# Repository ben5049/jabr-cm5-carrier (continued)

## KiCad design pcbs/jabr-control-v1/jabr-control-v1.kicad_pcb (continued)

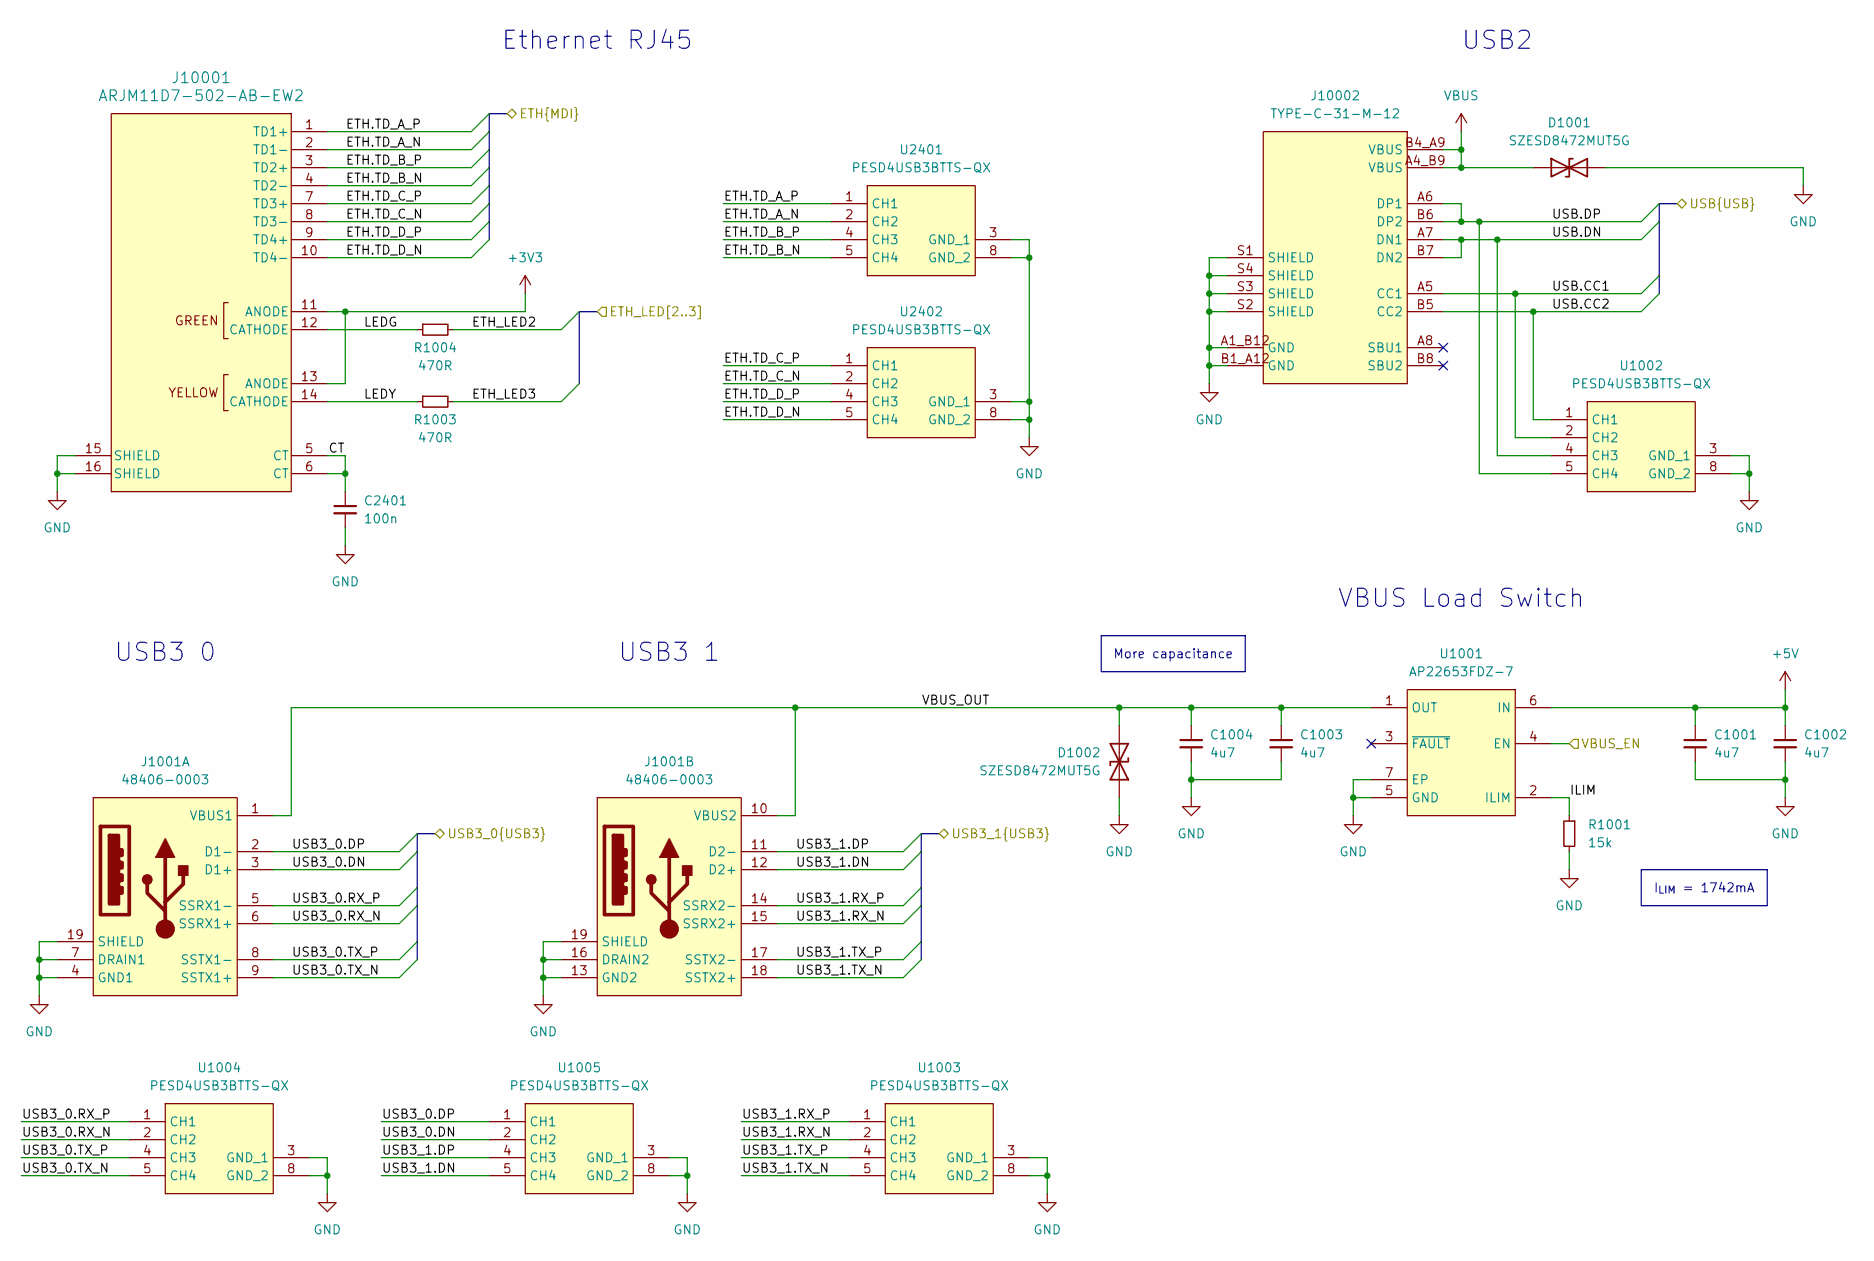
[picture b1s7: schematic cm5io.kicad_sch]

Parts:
C1001, C1002, C1003, C1004: 4u7; C_0402
C2401: 100n; C_0402
D1001, D1002: SZESD8472MUT5G; SZESD7462N2T5G
J1001: 48406-0003
J10001: ARJM11D7-502-AB-EW2; ARJM11D7-502-AB-EW2_ABR
J10002: TYPE-C-31-M-12; PARTREV 2020.12.08
R1001: 15k
R1003, R1004: 470R
U1001: AP22653FDZ-7; SON65P200X200X80-7N-D
U1002, U1003, U1004, U1005, U2401, U2402: PESD4USB3BTTS-QX; PESD4USB3BTTSQX; Mouser Part Number 771-PESD4USB3BTTS-QX

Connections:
+3V3: J10001.11 (ANODE), J10001.13 (ANODE); also elsewhere on the board
+5V: C1001.1, C1002.1, U1001.6 (IN); also elsewhere on the board
/CM5/ETH.TD_A_N: J10001.2 (TD1-), U2401.2 (CH2), U2401.9 (NC); also elsewhere on the board
/CM5/ETH.TD_A_P: J10001.1 (TD1+), U2401.1 (CH1), U2401.10 (NC); also elsewhere on the board
/CM5/ETH.TD_B_N: J10001.4 (TD2-), U2401.5 (CH4), U2401.6 (NC); also elsewhere on the board
/CM5/ETH.TD_B_P: J10001.3 (TD2+), U2401.4 (CH3), U2401.7 (NC); also elsewhere on the board
/CM5/ETH.TD_C_N: J10001.8 (TD3-), U2402.2 (CH2), U2402.9 (NC); also elsewhere on the board
/CM5/ETH.TD_C_P: J10001.7 (TD3+), U2402.1 (CH1), U2402.10 (NC); also elsewhere on the board
/CM5/ETH.TD_D_N: J10001.10 (TD4-), U2402.5 (CH4), U2402.6 (NC); also elsewhere on the board
/CM5/ETH.TD_D_P: J10001.9 (TD4+), U2402.4 (CH3), U2402.7 (NC); also elsewhere on the board
/CM5/USB2_DEV.CC1: J10002.A5 (CC1), U1002.2 (CH2), U1002.9 (NC); also elsewhere on the board
/CM5/USB2_DEV.CC2: J10002.B5 (CC2), U1002.1 (CH1), U1002.10 (NC); also elsewhere on the board
/CM5/USB2_DEV.DN: J10002.A7 (DN1), J10002.B7 (DN2), U1002.4 (CH3), U1002.7 (NC); also elsewhere on the board
/CM5/USB2_DEV.DP: J10002.A6 (DP1), J10002.B6 (DP2), U1002.5 (CH4), U1002.6 (NC); also elsewhere on the board
/CM5/USB3_0.DN: J1001.3 (D1+), U1005.2 (CH2), U1005.9 (NC); also elsewhere on the board
/CM5/USB3_0.DP: J1001.2 (D1-), U1005.1 (CH1), U1005.10 (NC); also elsewhere on the board
/CM5/USB3_0.RX_N: J1001.6 (SSRX1+), U1004.2 (CH2), U1004.9 (NC); also elsewhere on the board
/CM5/USB3_0.RX_P: J1001.5 (SSRX1-), U1004.1 (CH1), U1004.10 (NC); also elsewhere on the board
/CM5/USB3_0.TX_N: J1001.9 (SSTX1+), U1004.5 (CH4), U1004.6 (NC); also elsewhere on the board
/CM5/USB3_0.TX_P: J1001.8 (SSTX1-), U1004.4 (CH3), U1004.7 (NC); also elsewhere on the board
/CM5/USB3_1.DN: J1001.12 (D2+), U1005.5 (CH4), U1005.6 (NC); also elsewhere on the board
/CM5/USB3_1.DP: J1001.11 (D2-), U1005.4 (CH3), U1005.7 (NC); also elsewhere on the board
/CM5/USB3_1.RX_N: J1001.15 (SSRX2+), U1003.2 (CH2), U1003.9 (NC); also elsewhere on the board
/CM5/USB3_1.RX_P: J1001.14 (SSRX2-), U1003.1 (CH1), U1003.10 (NC); also elsewhere on the board
/CM5/USB3_1.TX_N: J1001.18 (SSTX2+), U1003.5 (CH4), U1003.6 (NC); also elsewhere on the board
/CM5/USB3_1.TX_P: J1001.17 (SSTX2-), U1003.4 (CH3), U1003.7 (NC); also elsewhere on the board
/CM5/VBUS_EN: U1001.4 (EN); also elsewhere on the board
/CM5IO/CT: C2401.1, J10001.5 (CT), J10001.6 (CT)
/CM5IO/ILIM: R1001.1, U1001.2 (ILIM)
/CM5IO/LEDG: J10001.12 (CATHODE), R1004.1
/CM5IO/LEDY: J10001.14 (CATHODE), R1003.1
/CM5IO/VBUS_OUT: C1003.1, C1004.1, D1002.2 (A2), J1001.1 (VBUS1), J1001.10 (VBUS2), U1001.1 (OUT)
GND: C1001.2, C1002.2, C1003.2, C1004.2, C2401.2, D1001.2 (A2), D1002.1 (A1), J1001.4 (GND1), J1001.7 (DRAIN1), J1001.13 (GND2), J1001.16 (DRAIN2), J1001.19 (SHIELD), J10001.15 (SHIELD), J10001.16 (SHIELD), J10002.A1_B12 (GND), J10002.B1_A12 (GND), J10002.S1 (SHIELD), J10002.S2 (SHIELD), J10002.S3 (SHIELD), J10002.S4 (SHIELD), R1001.2, U1001.5 (GND), U1001.7 (EP), U1002.3 (GND_1), U1002.8 (GND_2), U1003.3 (GND_1), U1003.8 (GND_2), U1004.3 (GND_1), U1004.8 (GND_2), U1005.3 (GND_1), U1005.8 (GND_2), U2401.3 (GND_1), U2401.8 (GND_2), U2402.3 (GND_1), U2402.8 (GND_2); also elsewhere on the board
VBUS: D1001.1 (A1), J10002.A4_B9 (VBUS), J10002.B4_A9 (VBUS); also elsewhere on the board

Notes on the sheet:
Ethernet RJ45
USB2
USB3 0
USB3 1
VBUS Load Switch
I_{LIM} = 1742mA
More capacitance

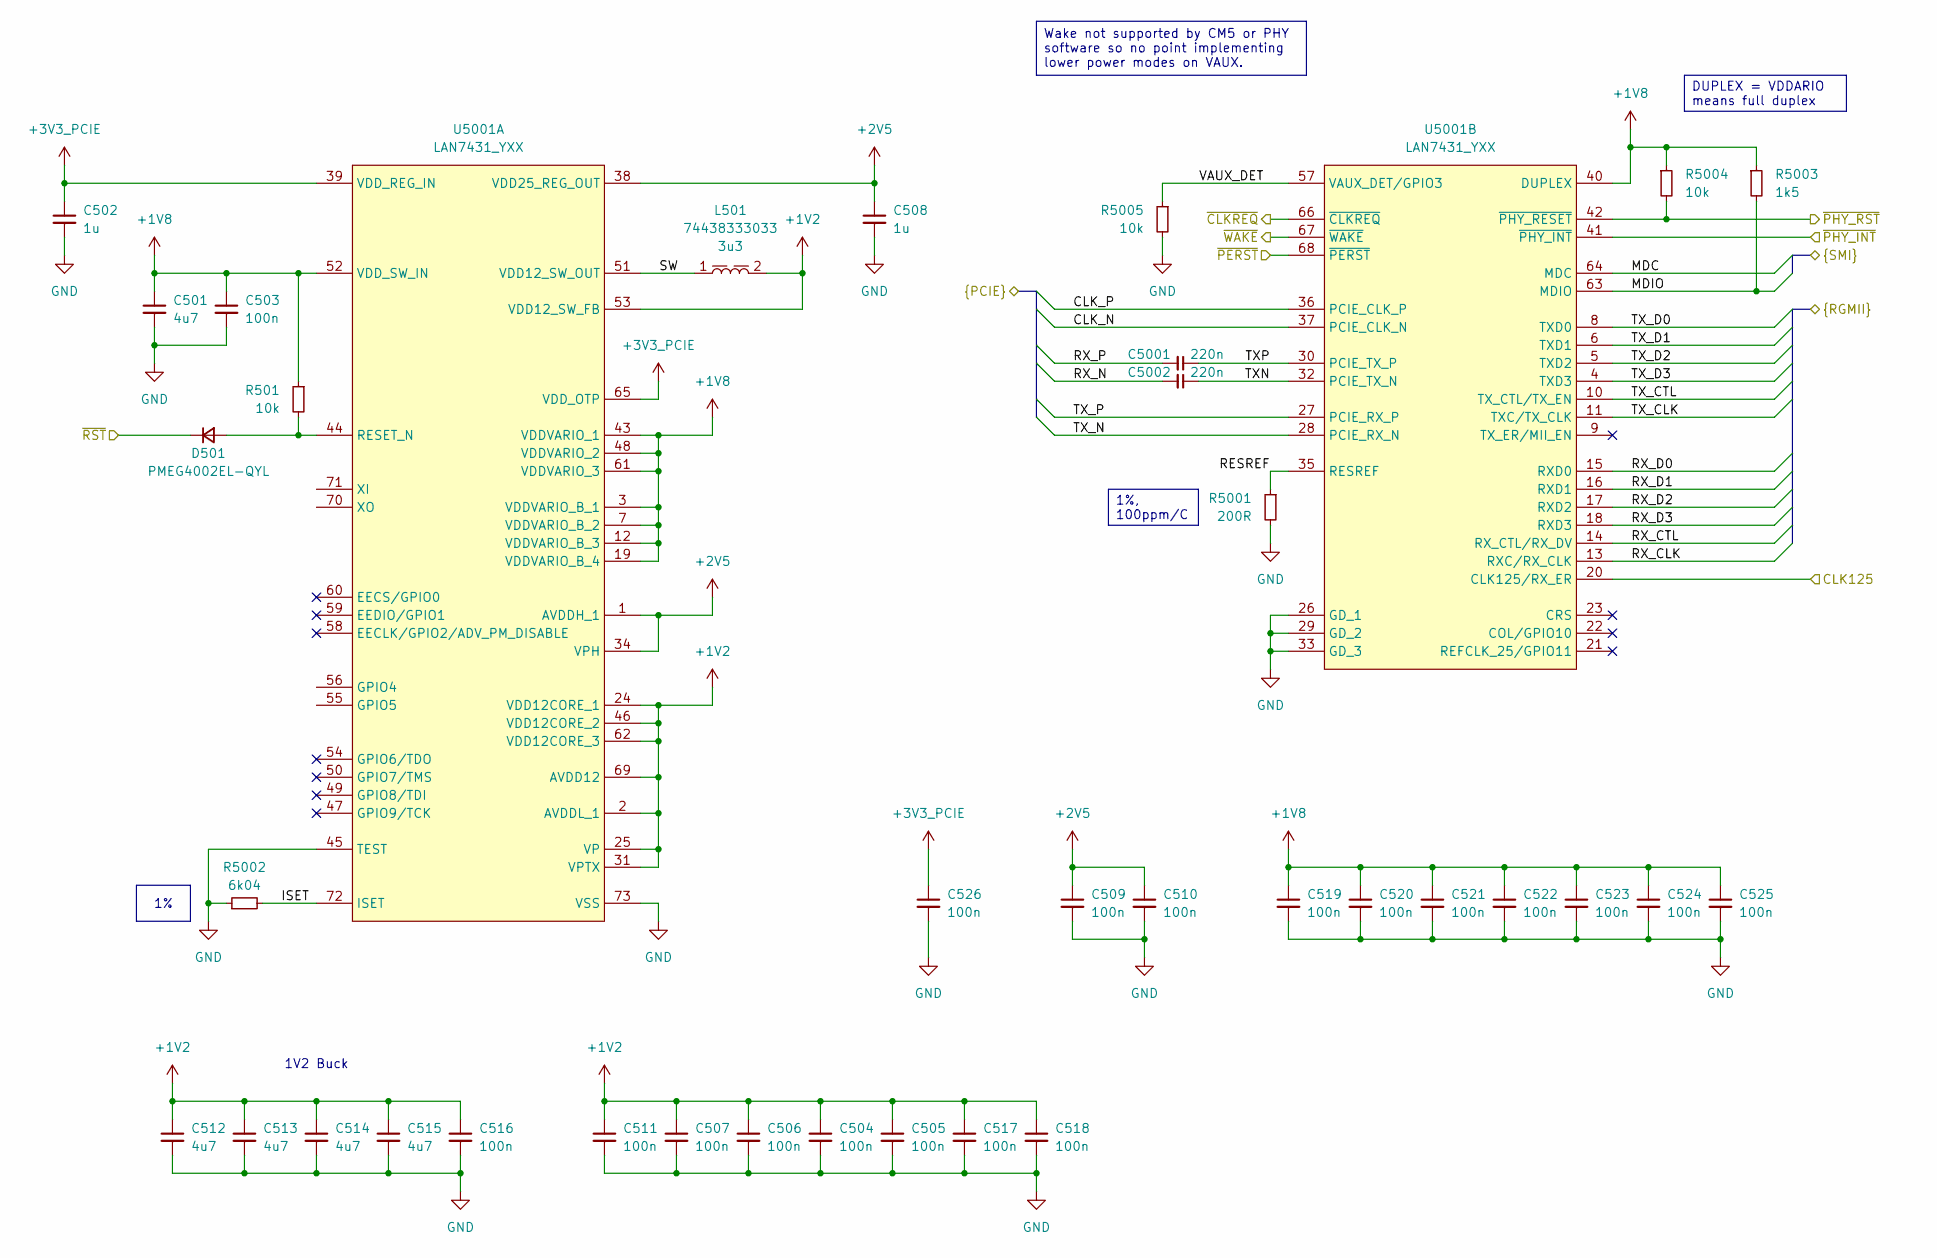
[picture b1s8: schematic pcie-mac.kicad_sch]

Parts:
C501, C512, C513, C514, C515: 4u7; C_0402
C502, C508: 1u; C_0402
C503, C504, C505, C506, C507, C509, C510, C511, C516, C517, C518, C519, C520, C521, C522, C523, C524, C525, C526: 100n; C_0402
C5001, C5002: 220n; C_0402
D501: PMEG4002EL-QYL
L501: 74438333033; L_Wurth_WE-MAPI-3010; Part Number 74438333033
R501, R5004, R5005: 10k; R_0402
R5001: 200R; R_0402
R5002: 6k04
R5003: 1k5; R_0402
U5001: LAN7431_YXX; QFN50P1000X1000X100-73N-D; Mouser Part Number 579-LAN7431/YXX

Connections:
+1V2: C504.1, C505.1, C506.1, C507.1, C511.1, C512.1, C513.1, C514.1, C515.1, C516.1, C517.1, C518.1, L501.2, U5001.2 (AVDDL_1), U5001.24 (VDD12CORE_1), U5001.25 (VP), U5001.31 (VPTX), U5001.46 (VDD12CORE_2), U5001.53 (VDD12_SW_FB), U5001.62 (VDD12CORE_3), U5001.69 (AVDD12)
+1V8: C501.1, C503.1, C519.1, C520.1, C521.1, C522.1, C523.1, C524.1, C525.1, R501.1, R5003.1, R5004.1, U5001.3 (VDDVARIO_B_1), U5001.7 (VDDVARIO_B_2), U5001.12 (VDDVARIO_B_3), U5001.19 (VDDVARIO_B_4), U5001.40 (DUPLEX), U5001.43 (VDDVARIO_1), U5001.48 (VDDVARIO_2), U5001.52 (VDD_SW_IN), U5001.61 (VDDVARIO_3); also elsewhere on the board
+2V5: C508.1, C509.1, C510.1, U5001.1 (AVDDH_1), U5001.34 (VPH), U5001.38 (VDD25_REG_OUT)
+3V3_PCIE: C502.1, C526.1, U5001.39 (VDD_REG_IN), U5001.65 (VDD_OTP); also elsewhere on the board
/CM5/~PCIE_CLKREQ: U5001.66 (~CLKREQ); also elsewhere on the board
/CM5/~PCIE_WAKE: U5001.67 (~WAKE); also elsewhere on the board
/CM5/~RST_5V: D501.1 (K); also elsewhere on the board
/PCIe Switch/PORT2.CLK_N: U5001.37 (PCIE_CLK_N); also elsewhere on the board
/PCIe Switch/PORT2.CLK_P: U5001.36 (PCIE_CLK_P); also elsewhere on the board
/PCIe Switch/PORT2.RX_N: C5002.2; also elsewhere on the board
/PCIe Switch/PORT2.RX_P: C5001.2; also elsewhere on the board
/PCIe Switch/PORT2.TX_N: U5001.28 (PCIE_RX_N); also elsewhere on the board
/PCIe Switch/PORT2.TX_P: U5001.27 (PCIE_RX_P); also elsewhere on the board
/PCIe Switch/~PORT2_RST: U5001.68 (~PERST); also elsewhere on the board
/PCIe to 1000BASE-T1/1000BASE-T1 PHY/MDC: U5001.64 (MDC); also elsewhere on the board
/PCIe to 1000BASE-T1/1000BASE-T1 PHY/MDIO: R5003.2, U5001.63 (MDIO); also elsewhere on the board
/PCIe to 1000BASE-T1/1000BASE-T1 PHY/RX_CLK: U5001.13 (RXC/RX_CLK); also elsewhere on the board
/PCIe to 1000BASE-T1/1000BASE-T1 PHY/RX_CTL: U5001.14 (RX_CTL/RX_DV); also elsewhere on the board
/PCIe to 1000BASE-T1/1000BASE-T1 PHY/RX_D0: U5001.15 (RXD0); also elsewhere on the board
/PCIe to 1000BASE-T1/1000BASE-T1 PHY/RX_D1: U5001.16 (RXD1); also elsewhere on the board
/PCIe to 1000BASE-T1/1000BASE-T1 PHY/RX_D2: U5001.17 (RXD2); also elsewhere on the board
/PCIe to 1000BASE-T1/1000BASE-T1 PHY/RX_D3: U5001.18 (RXD3); also elsewhere on the board
/PCIe to 1000BASE-T1/1000BASE-T1 PHY/TX_CLK: U5001.11 (TXC/TX_CLK); also elsewhere on the board
/PCIe to 1000BASE-T1/1000BASE-T1 PHY/TX_CTL: U5001.10 (TX_CTL/TX_EN); also elsewhere on the board
/PCIe to 1000BASE-T1/1000BASE-T1 PHY/TX_D0: U5001.8 (TXD0); also elsewhere on the board
/PCIe to 1000BASE-T1/1000BASE-T1 PHY/TX_D1: U5001.6 (TXD1); also elsewhere on the board
/PCIe to 1000BASE-T1/1000BASE-T1 PHY/TX_D2: U5001.5 (TXD2); also elsewhere on the board
/PCIe to 1000BASE-T1/1000BASE-T1 PHY/TX_D3: U5001.4 (TXD3); also elsewhere on the board
/PCIe to 1000BASE-T1/1000BASE-T1 PHY/~RST: R5004.2, U5001.42 (~PHY_RESET); also elsewhere on the board
/PCIe to 1000BASE-T1/PCIe MAC/ISET: R5002.2, U5001.72 (ISET)
/PCIe to 1000BASE-T1/PCIe MAC/RESREF: R5001.1, U5001.35 (RESREF)
/PCIe to 1000BASE-T1/PCIe MAC/SW: L501.1, U5001.51 (VDD12_SW_OUT)
/PCIe to 1000BASE-T1/PCIe MAC/TXN: C5002.1, U5001.32 (PCIE_TX_N)
/PCIe to 1000BASE-T1/PCIe MAC/TXP: C5001.1, U5001.30 (PCIE_TX_P)
/PCIe to 1000BASE-T1/PCIe MAC/VAUX_DET: R5005.1, U5001.57 (VAUX_DET/GPIO3)
GND: C501.2, C502.2, C503.2, C504.2, C505.2, C506.2, C507.2, C508.2, C509.2, C510.2, C511.2, C512.2, C513.2, C514.2, C515.2, C516.2, C517.2, C518.2, C519.2, C520.2, C521.2, C522.2, C523.2, C524.2, C525.2, C526.2, R5001.2, R5002.1, R5005.2, U5001.26 (GD_1), U5001.29 (GD_2), U5001.33 (GD_3), U5001.45 (TEST), U5001.73 (VSS); also elsewhere on the board
unnamed: D501.2 (A), R501.2, U5001.44 (RESET_N)

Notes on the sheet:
1V2 Buck
DUPLEX = VDDARIO means full duplex
1%, 100ppm/C
Wake not supported by CM5 or PHY software so no point implementing lower power modes on VAUX.

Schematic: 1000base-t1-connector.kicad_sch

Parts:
C302, C601: 100n; C_0603; Voltage 100V
D302, D601: SZESD7241N2T5G; SZESD7462N2T5G; Mouser Part Number 863-SZESD7241N2T5G
D303: 824012823; Mouser Part Number 710-824012823
FL301: ACT1210G-800-2P-TL10; ACT1210G; Mouser Part Number 810-ACT1210G8002PTL1
J6001: MSPE-J2L0-x00; MSPEJ2L0x00; Mouser Part Number 523-MSPE-J2L0-B00

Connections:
/PCIe to 1000BASE-T1/1000BASE-T1 Connector/CMC_TRXN: C302.1, FL301.2
/PCIe to 1000BASE-T1/1000BASE-T1 Connector/CMC_TRXP: C601.1, FL301.1
/PCIe to 1000BASE-T1/1000BASE-T1 Connector/CONN_TRXN: C302.2, D601.2 (A2), J6001.2 (TRXN)
/PCIe to 1000BASE-T1/1000BASE-T1 Connector/CONN_TRXP: C601.2, D302.2 (A2), J6001.1 (TRXP)
/PCIe to 1000BASE-T1/1000BASE-T1 Connector/TRXN: D303.1, D303.6, FL301.3; also elsewhere on the board
/PCIe to 1000BASE-T1/1000BASE-T1 Connector/TRXP: D303.2, D303.5, FL301.4; also elsewhere on the board
GND: D302.1 (A1), D303.3, D303.4, D601.1 (A1); also elsewhere on the board

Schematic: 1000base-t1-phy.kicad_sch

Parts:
C2935, C2936: 10p; C_0402
R801, R803, R804, R805, R806, R807, R808, R809, R8002: 10k; R_0402
R8001: 12k1; R_0402
TP801, TP8001, TP8002: 1.5mm; TestPoint_Pad_D1.5mm
U8001: LAN8870; lan8870
Y8001: XRCGB25M000F3A16R0

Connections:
+1V1: U8001.5 (VDDACORE), U8001.10 (VDDCORE), U8001.19 (VDDCORE), U8001.29 (VDDCORE), U8001.44 (VDDACORE), U8001.46 (VDDACORE); also elsewhere on the board
+1V8: R804.1, R809.1, R8002.1, U8001.13 (VDD_RGMII), U8001.20 (VDD_RGMII_VPH), U8001.36 (VDDIO); also elsewhere on the board
+3V3_AON: U8001.1 (VBAT); also elsewhere on the board
+3V3_PCIE: U8001.9 (VDD_REG); also elsewhere on the board
/PCIe to 1000BASE-T1/1000BASE-T1 Connector/TRXN: U8001.42 (TRXN); also elsewhere on the board
/PCIe to 1000BASE-T1/1000BASE-T1 Connector/TRXP: U8001.43 (TRXP); also elsewhere on the board
/PCIe to 1000BASE-T1/1000BASE-T1 PHY/1588_CLK_ADJ: TP8002.1, U8001.38 (LED1/GPIO1)
/PCIe to 1000BASE-T1/1000BASE-T1 PHY/EXTRES: R8001.1, U8001.47 (EXTRES)
/PCIe to 1000BASE-T1/1000BASE-T1 PHY/MDC: U8001.34 (MDC); also elsewhere on the board
/PCIe to 1000BASE-T1/1000BASE-T1 PHY/MDIO: U8001.33 (MDIO); also elsewhere on the board
/PCIe to 1000BASE-T1/1000BASE-T1 PHY/MODE: R808.1, TP801.1, U8001.18 (1588_EVT/MODE_STRP)
/PCIe to 1000BASE-T1/1000BASE-T1 PHY/OSC_IN: C2935.2, U8001.6 (XTAL1), Y8001.3
/PCIe to 1000BASE-T1/1000BASE-T1 PHY/OSC_OUT: C2936.2, U8001.7 (XTAL2), Y8001.1
/PCIe to 1000BASE-T1/1000BASE-T1 PHY/REG_EN: R801.1, U8001.8 (REG_EN)
/PCIe to 1000BASE-T1/1000BASE-T1 PHY/RX_CLK: U8001.16 (RX_CLK); also elsewhere on the board
/PCIe to 1000BASE-T1/1000BASE-T1 PHY/RX_CTL: R805.1, U8001.17 (RX_CTL); also elsewhere on the board
/PCIe to 1000BASE-T1/1000BASE-T1 PHY/RX_D0: R804.2, U8001.11 (RX_D0); also elsewhere on the board
/PCIe to 1000BASE-T1/1000BASE-T1 PHY/RX_D1: R807.1, U8001.12 (RX_D1); also elsewhere on the board
/PCIe to 1000BASE-T1/1000BASE-T1 PHY/RX_D2: R806.1, U8001.14 (RX_D2); also elsewhere on the board
/PCIe to 1000BASE-T1/1000BASE-T1 PHY/RX_D3: R803.1, U8001.15 (RX_D3); also elsewhere on the board
/PCIe to 1000BASE-T1/1000BASE-T1 PHY/S_VP: TP8001.1, U8001.22 (S_VP)
/PCIe to 1000BASE-T1/1000BASE-T1 PHY/TX_CLK: U8001.23 (TX_CLK); also elsewhere on the board
/PCIe to 1000BASE-T1/1000BASE-T1 PHY/TX_CTL: U8001.24 (TX_CTL); also elsewhere on the board
/PCIe to 1000BASE-T1/1000BASE-T1 PHY/TX_D0: U8001.25 (TX_D0); also elsewhere on the board
/PCIe to 1000BASE-T1/1000BASE-T1 PHY/TX_D1: U8001.26 (TX_D1); also elsewhere on the board
/PCIe to 1000BASE-T1/1000BASE-T1 PHY/TX_D2: U8001.27 (TX_D2); also elsewhere on the board
/PCIe to 1000BASE-T1/1000BASE-T1 PHY/TX_D3: U8001.28 (TX_D3); also elsewhere on the board
/PCIe to 1000BASE-T1/1000BASE-T1 PHY/~RST: U8001.39 (~RST); also elsewhere on the board
/PCIe to 1000BASE-T1/INH: U8001.4 (INH); also elsewhere on the board
GND: C2935.1, C2936.1, R801.2, R803.2, R805.2, R806.2, R807.2, R808.2, R8001.2, U8001.3 (WAKE_IN), U8001.49 (EP), Y8001.2, Y8001.4; also elsewhere on the board
unnamed: U8001.37 (VDDA_PVT), U8001.41 (VDDA), U8001.45 (VDDA), U8001.48 (VDDA)

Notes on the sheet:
~{100M}/1G
SLAVE/~{MASTER}
AUTO_NEG
PHYAD1
PPS
PHYAD0
AUTONOMOUS/~{MANAGED}
Reference schematic
connect vdda
INH Pulled down in 5V regulator schematic
Add decoupling caps
The reference schematic uses a VXM7-9013-25M0000000 which is very expensive
When in managed mode: - SPEED_SEL = PHYAD4 - AUTO_NEG = PHYAD3 - MODE = PHYAD2 ∴ PHYAD = 0b11000 = 0x18

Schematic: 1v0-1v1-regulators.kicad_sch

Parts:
C1501, C1502, C1504, C1505, C1506, C3801, C3802, C3805, C3806, C3807: 4u7; C_0402
C1503, C3804: 22p; C_0402
L1501, L3801: 78438313015; L_Wurth_WE-MAIA-1610; Part Number 78438313015
R1501: 120k; R_0402
R1502, R3802: 180k; R_0402
R3801: 150k; R_0402
TP1501, TP3801: 1.5mm; TestPoint_Pad_D1.5mm
U1501, U3801: TPS62290TDRVRQ1; SON65P200X200X80-7N; Mouser Part Number 595-TPS62290TDRVRQ1

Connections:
+1V0: C1503.1, C1504.1, C1505.1, C1506.1, L1501.2, R1501.1, TP1501.1; also elsewhere on the board
+1V1: C3804.1, C3805.1, C3806.1, C3807.1, L3801.2, R3801.1, TP3801.1; also elsewhere on the board
+5V: C1501.1, C1502.1, C3801.1, C3802.1, U1501.4 (EN), U1501.5 (VIN), U3801.4 (EN), U3801.5 (VIN); also elsewhere on the board
/Power/1V0 & 1V1 Regulators/FB: C1503.2, C3804.2, R1501.2, R1502.1, R3801.2, R3802.1, U1501.3 (FB), U3801.3 (FB)
/Power/1V0 & 1V1 Regulators/SW: L1501.1, L3801.1, U1501.1 (SW), U3801.1 (SW)
GND: C1501.2, C1502.2, C1504.2, C1505.2, C1506.2, C3801.2, C3802.2, C3805.2, C3806.2, C3807.2, R1502.2, R3802.2, U1501.2 (MODE), U1501.6 (GND), U1501.7 (EP), U3801.2 (MODE), U3801.6 (GND), U3801.7 (EP); also elsewhere on the board

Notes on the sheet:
1V0 Regulator
1V1 Regulator
Pulling MODE low enters power saving mode at low current draws
Use high quality, low ESR (<50mΩ) capacitors such as GRM155R61A475ME02

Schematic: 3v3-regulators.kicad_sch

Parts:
C401, C402: 10u; C_0805
C403, C405: 1u; C_0402
C404: 1u; C_0402; Voltage 50V
C406, C407, C1401, C1402, C1403, C1404, C1405, C1406, C1407, C1408, C1409, C1410, C1412, C1413, C1414: 4u7; C_0402
C1411: 22p; C_0402
L401: 74479335329222; L_Wurth_WE-PMFI-353220; Part Number 74479335329222
L1401: 78438313015; L_Wurth_WE-MAIA-1610; Part Number 78438313015
R401: 10k; R_0402; not fitted
R402: 10k; R_0402
R403: 100k; R_0402
R1401: 810k; R_0402
R1402: 180k; R_0402
TP401, TP1401, TP1402: 1.5mm; TestPoint_Pad_D1.5mm
U401: LMQ66430MC3RXBRQ1; LMQ664x0
U402: TPS7B8133QDRVRQ1; SON65P200X200X80-7N; Mouser Part Number 595-TPS7B8133QDRVRQ1
U403: TPS2116DRL; SOTFL50P160X60-8N
U1401: TPS62290TDRVRQ1; SON65P200X200X80-7N; Mouser Part Number 595-TPS62290TDRVRQ1

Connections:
+3V3: U403.3 (VIN1), U403.5 (MODE); also elsewhere on the board
+3V3_AON: TP401.1, U403.2 (VOUT), U403.7 (VOUT); also elsewhere on the board
+3V3_M2: C406.1, C407.1, C1401.1, C1402.1, C1403.1, C1404.1, C1405.1, C1406.1, C1407.1, C1408.1, L401.2, R403.2, TP1401.1, U401.11 (VOUT/FB); also elsewhere on the board
+3V3_PCIE: C1411.1, C1412.1, C1413.1, C1414.1, L1401.2, R1401.1, TP1402.1; also elsewhere on the board
+5V: C401.1, C402.1, C1409.1, C1410.1, U401.3 (VIN), U1401.4 (EN), U1401.5 (VIN); also elsewhere on the board
+VIN: C404.1, U402.1 (IN), U402.2 (EN); also elsewhere on the board
/CM5/PCIE_PWR_EN: R401.1, U401.1 (EN/UVLO), U401.16 (EN/UVLO); also elsewhere on the board
/Power/3V3 Regulators/3V3_AON_RAW: C405.1, U402.6 (OUT), U403.6 (VIN2)
/Power/3V3 Regulators/3V3_M2_MODE: R402.1, U401.13 (MODE/SYNC)
/Power/3V3 Regulators/3V3_PG: R403.1, U401.14 (PG), U403.4 (PR1)
/Power/3V3 Regulators/FB: C1411.2, R1401.2, R1402.1, U1401.3 (FB)
/Power/3V3 Regulators/SW: L401.1, L1401.1, U401.7 (SW), U1401.1 (SW)
/Power/3V3 Regulators/VCC: C403.1, U401.10 (VCC)
GND: C401.2, C402.2, C403.2, C404.2, C405.2, C406.2, C407.2, C1401.2, C1402.2, C1403.2, C1404.2, C1405.2, C1406.2, C1407.2, C1408.2, C1409.2, C1410.2, C1412.2, C1413.2, C1414.2, R401.2, R402.2, R1402.2, U401.6 (PGND), U401.15 (GND/DAP), U402.3 (GND), U402.4 (GND), U402.7 (EP), U403.1 (GND), U1401.2 (MODE), U1401.6 (GND), U1401.7 (EP); also elsewhere on the board

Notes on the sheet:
3V3 M.2 Regulator
3V3 PCIe Regulator
3V3 Always on supply
3V3_AON switchover to use most efficient supply.
Use high quality, low ESR (<50mΩ) capacitors such as GRM155R61A475ME02
150mA Max
EN is set by CM5
MODE is auto by default. Setting MODE high means a lower output ripple.
3A Max
PR1 > 1V => VOUT = VIN1 PR1 < 1V => VOUT = VIN2

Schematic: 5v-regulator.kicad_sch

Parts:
C1301, C1311: 22u; C_0805; Voltage 35V
C1302: 4u7; C_0805; Voltage 35V
C1303, C1312: 2n2; C_0402
C1304: 100n; C_0402
C1305: 2u2; C_0402
C1306: 100n; C_0402; Voltage 50V
C1307: 1n; C_0402
C1308: 4p7; C_0402
C1309, C1310: 22u; C_0805
C1313: 1u; C_0402
D2301: PMEG4002EL-QYL
L1301: 74438356018; L_Wurth_WE-MAPI-4020; Part Number 74438356018
Q2602: DMN21D2UFB-7B; DMN21D2UFB7B; Mouser Part Number 621-DMN21D2UFB-7B
R1301, R1306: 12k1; R_0402
R1302, R1308: 100k; R_0402
R1303: 22k; R_0402
R1304: 10k; R_0402
R1305: 680R; R_0402
R1307: 33k; R_0402
TP1301: 1.5mm; TestPoint_Pad_D1.5mm
U1201: TPS259472ARPWR
U1301: MAX20004AFOC/VY+T; MAX20004AFOC_VY+; Manufacturer_Part_Number MAX20004AFOA/VY+T; Mouser Part Number 700-MAX20004AFOA/VYT

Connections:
+3V3_AON: R1302.1, R1308.1; also elsewhere on the board
+5V: C1309.1, C1310.1, L1301.2, R1307.1, TP1301.1, U1201.6 (OUT), U1301.1 (OUT); also elsewhere on the board
/PCIe to 1000BASE-T1/INH: D2301.1 (K), R1304.1; also elsewhere on the board
/Power/5V Regulator/5V_EN: D2301.2 (A), Q2602.3 (D), R1302.2, U1301.11 (EN)
/Power/5V Regulator/BST: C1306.1, U1301.3 (BST)
/Power/5V Regulator/DVDT: C1312.1, U1201.7 (DVDT), U1201.14 (DVDT)
/Power/5V Regulator/ILIM: R1305.1, U1201.9 (ILM)
/Power/5V Regulator/ITIMER: C1303.1, U1201.10 (ITIMER), U1201.11 (ITIMER)
/Power/5V Regulator/LX: C1306.2, L1301.1, U1301.6 (LX)
/Power/5V Regulator/PGTH: R1306.1, R1307.2, U1201.4 (PGTH), U1201.13 (PGTH)
/Power/5V Regulator/VBUS_PG: Q2602.1 (G), R1308.2, U1201.3 (PG)
/Power/5V Regulator/VIN_BIAS: C1305.1, U1301.13 (BIAS), U1301.16 (FB)
/Power/5V Regulator/VIN_COMP: C1308.1, R1303.1, U1301.15 (COMP)
/Power/5V Regulator/VIN_COMP2: C1307.1, R1303.2
/Power/5V Regulator/VIN_FOSC: R1301.1, U1301.17 (FOSC)
GND: C1301.2, C1302.2, C1303.2, C1304.2, C1305.2, C1307.2, C1308.2, C1309.2, C1310.2, C1311.2, C1312.2, C1313.2, Q2602.2 (S), R1301.2, R1304.2, R1305.2, R1306.2, U1201.8 (GND), U1301.4 (PGND_1), U1301.5 (PGND_2), U1301.7 (PGND_3), U1301.8 (PGND_4), U1301.12 (SYNC), U1301.14 (GND); also elsewhere on the board
VBUS: C1313.1, U1201.1 (EN/UVLO), U1201.5 (IN), U1201.12 (EN/UVLO); also elsewhere on the board
VIN: C1301.1, C1302.1, C1304.1, C1311.1, U1301.9 (SUPSW), U1301.10 (SUP)

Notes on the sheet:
These components must be located on the USB-C connector side of the break line
5V Regulator
5V OR-ing Circuitry
VBUS eFuse
V_{PGTH} = 4.5V
INH signal is connected to +3V3_AON through a PMOS in the ethernet PHY. Normally the PHY asserts INH, keeping it high. When the PHY wants to enter sleep mode it deasserts INH, which gets pulled to GND by the resistor. When VBUS is present, all of this behavior is overridden, and 5V_EN is kept low.
L_{MIN} = 1.5uH for 24V -> 5V at 2.2MHz. Chose 1.8uH
Add LEDs
32uF of output capacitance required for 2A load change to cause a 100mV droop
I_{MAX} = 4.9A
29uF of input capacitance required for 10mV ripple at 24V -> 5V and 2.2MHz

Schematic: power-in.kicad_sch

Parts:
C301: 100n; C_0603; Voltage 100V
D301: SZESD7241N2T5G; SZESD7462N2T5G; Mouser Part Number 863-SZESD7241N2T5G
J9001: 43045-0201; 43045-02YY; Mouser Part Number 538-43045-0201
R301: 120k; R_0402
R302, R304: 10k; R_0402
R303: 4k7; R_0402
U301: TVS3301DRBR; SON65P300X300X100-9N-D
U302: TPS26600RHFR; QFN50P400X500X100-25N-D; Mouser Part Number 595-TPS26601RHFR

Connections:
+VIN: U302.23 (OUT_1), U302.24 (OUT_2); also elsewhere on the board
/Power/Power In/ILIM: R304.2, U302.19 (ILIM)
/Power/Power In/OVP: R302.2, R303.1, U302.12 (OVP)
/Power/Power In/RTN: R303.2, R304.1, U302.15 (RTN), U302.25 (EP)
/Power/Power In/UVLO: R301.2, R302.1, U302.10 (UVLO)
/Power/Power In/VIN_RAW: C301.2, D301.2 (A2), J9001.2 (+), R301.1, U301.1 (IN), U301.2 (IN), U301.3 (IN), U301.4 (IN), U302.8 (IN_1), U302.9 (IN_2)
/Power/Power In/~FLT: U302.22 (~FLT)
GND: C301.1, D301.1 (A1), J9001.1 (-), U301.5 (GND), U301.6 (GND), U301.7 (GND), U301.8 (GND), U302.17 (GND); also elsewhere on the board

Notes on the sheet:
Surge Protection
eFuse
UVLO = 10.9V OVP = 34.1V
R_{ILIM} = 10kΩ ∴ I_{LIM} = 1.2A
TPS26600 has auto-retry when a fault occurs.
ESD Protection

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
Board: 6 copper layers, 245 parts (4 on the bottom side), 165 nets, no tracks yet.
